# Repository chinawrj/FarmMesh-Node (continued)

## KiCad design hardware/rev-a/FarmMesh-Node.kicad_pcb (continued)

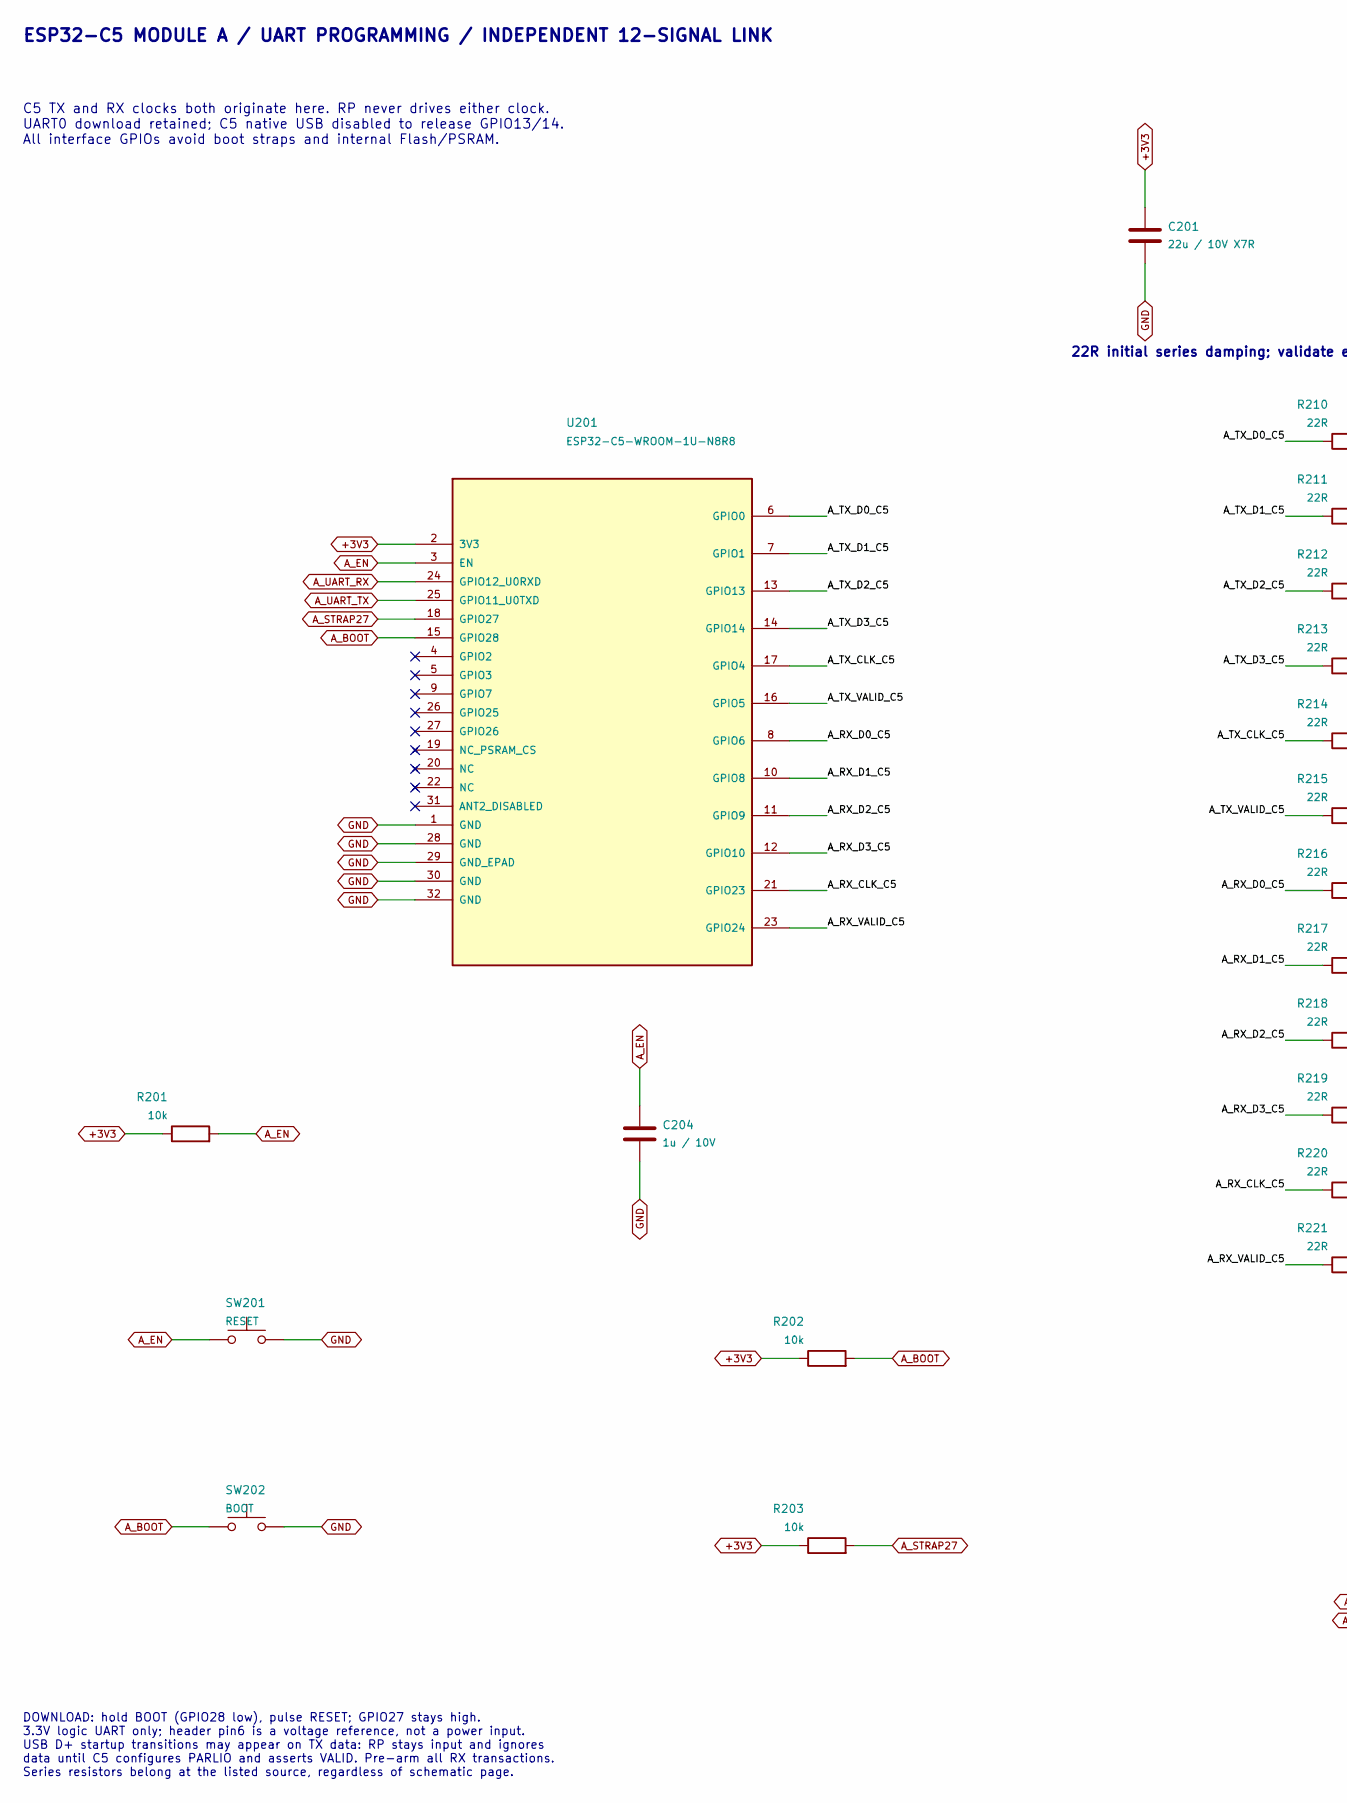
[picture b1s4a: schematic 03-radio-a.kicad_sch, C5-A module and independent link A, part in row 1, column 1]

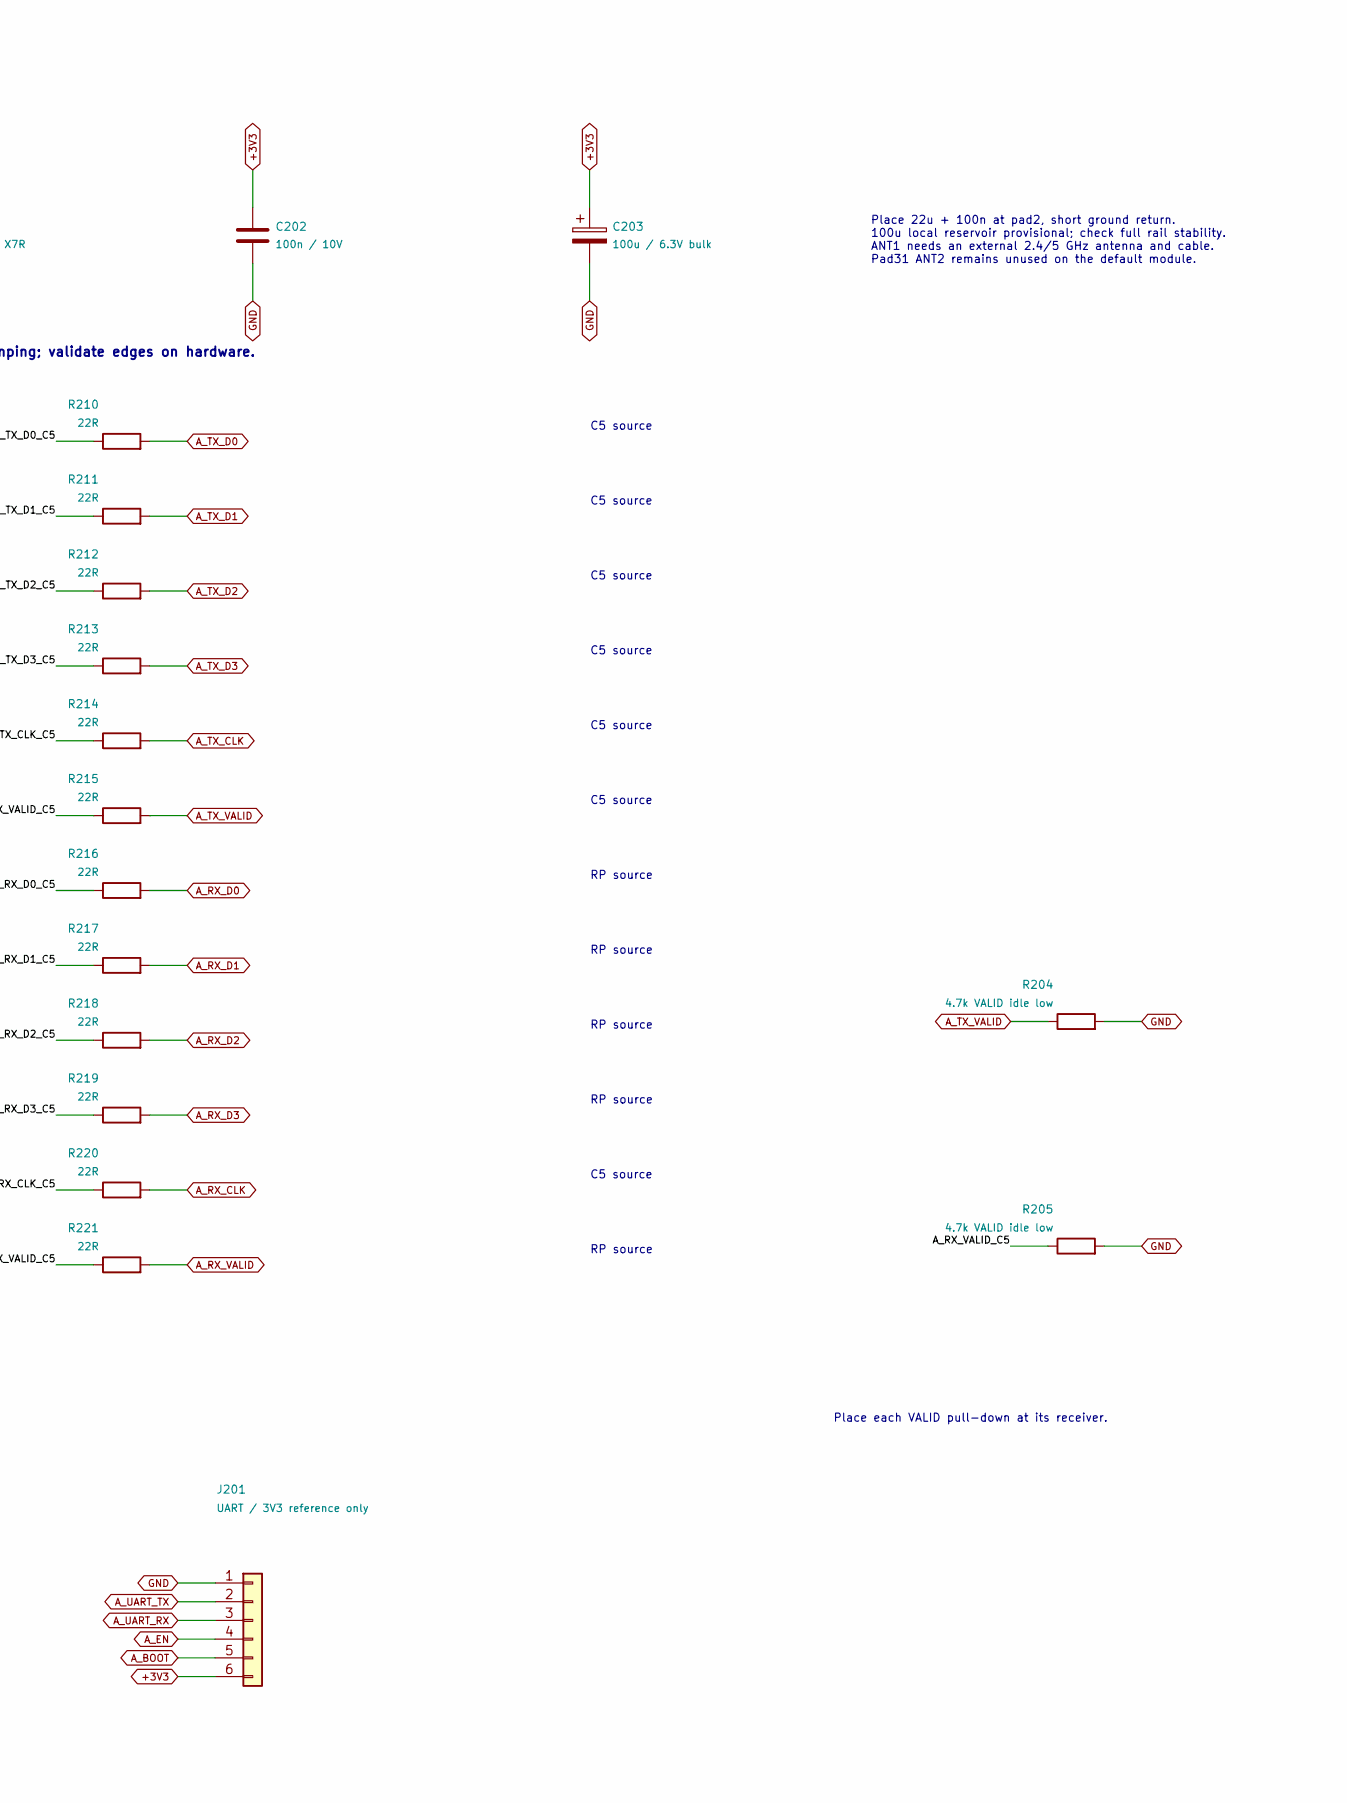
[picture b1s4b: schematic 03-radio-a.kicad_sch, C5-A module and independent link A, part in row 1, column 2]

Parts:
C201: 22u / 10V X7R; C_0805_2012Metric
C202: 100n / 10V; C_0603_1608Metric
C203: 100u / 6.3V bulk; CP_Elec_6.3x5.8
C204: 1u / 10V; C_0603_1608Metric
J201: UART / 3V3 reference only; PinHeader_1x06_P2.54mm_Vertical
R201, R202, R203: 10k; R_0603_1608Metric
R204, R205: 4.7k VALID idle low; R_0603_1608Metric
R210, R211, R212, R213, R214, R215, R216, R217, R218, R219, R220, R221: 22R; R_0603_1608Metric
SW201: RESET; SW_Push_1P1T_NO_E-Switch_TL3301NxxxxxG
SW202: BOOT; SW_Push_1P1T_NO_E-Switch_TL3301NxxxxxG
U201: ESP32-C5-WROOM-1U-N8R8; ESP32-C5-WROOM-1U; MPN ESP32-C5-WROOM-1U-N8R8

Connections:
+3V3: C201.1, C202.1, C203.1, J201.6, R201.1, R202.1, R203.1, U201.2 (3V3); also elsewhere on the board
/C5-A module and independent link A/A_RX_CLK_C5: R220.1, U201.21 (GPIO23)
/C5-A module and independent link A/A_RX_D0_C5: R216.1, U201.8 (GPIO6)
/C5-A module and independent link A/A_RX_D1_C5: R217.1, U201.10 (GPIO8)
/C5-A module and independent link A/A_RX_D2_C5: R218.1, U201.11 (GPIO9)
/C5-A module and independent link A/A_RX_D3_C5: R219.1, U201.12 (GPIO10)
/C5-A module and independent link A/A_RX_VALID_C5: R205.1, R221.1, U201.23 (GPIO24)
/C5-A module and independent link A/A_TX_CLK_C5: R214.1, U201.17 (GPIO4)
/C5-A module and independent link A/A_TX_D0_C5: R210.1, U201.6 (GPIO0)
/C5-A module and independent link A/A_TX_D1_C5: R211.1, U201.7 (GPIO1)
/C5-A module and independent link A/A_TX_D2_C5: R212.1, U201.13 (GPIO13)
/C5-A module and independent link A/A_TX_D3_C5: R213.1, U201.14 (GPIO14)
/C5-A module and independent link A/A_TX_VALID_C5: R215.1, U201.16 (GPIO5)
A_BOOT: J201.5, R202.2, SW202.1, U201.15 (GPIO28)
A_EN: C204.1, J201.4, R201.2, SW201.1, U201.3 (EN)
A_RX_CLK: R220.2; also elsewhere on the board
A_RX_D0: R216.2; also elsewhere on the board
A_RX_D1: R217.2; also elsewhere on the board
A_RX_D2: R218.2; also elsewhere on the board
A_RX_D3: R219.2; also elsewhere on the board
A_RX_VALID: R221.2; also elsewhere on the board
A_STRAP27: R203.2, U201.18 (GPIO27)
A_TX_CLK: R214.2; also elsewhere on the board
A_TX_D0: R210.2; also elsewhere on the board
A_TX_D1: R211.2; also elsewhere on the board
A_TX_D2: R212.2; also elsewhere on the board
A_TX_D3: R213.2; also elsewhere on the board
A_TX_VALID: R204.1, R215.2; also elsewhere on the board
A_UART_RX: J201.3, U201.24 (GPIO12_U0RXD)
A_UART_TX: J201.2, U201.25 (GPIO11_U0TXD)
GND: C201.2, C202.2, C203.2, C204.2, J201.1, R204.2, R205.2, SW201.2, SW202.2, U201.1 (GND), U201.28 (GND), U201.29 (GND_EPAD), U201.30 (GND), U201.32 (GND); also elsewhere on the board

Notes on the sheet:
22R initial series damping; validate edges on hardware.
ESP32-C5 MODULE A / UART PROGRAMMING / INDEPENDENT 12-SIGNAL LINK
Place each VALID pull-down at its receiver.
C5 source
RP source
Place 22u + 100n at pad2, short ground return. 100u local reservoir provisional; check full rail stability. ANT1 needs an external 2.4/5 GHz antenna and cable. Pad31 ANT2 remains unused on the default module.
C5 TX and RX clocks both originate here. RP never drives either clock. UART0 download retained; C5 native USB disabled to release GPIO13/14. All interface GPIOs avoid boot straps and internal Flash/PSRAM.
DOWNLOAD: hold BOOT (GPIO28 low), pulse RESET; GPIO27 stays high. 3.3V logic UART only; header pin6 is a voltage reference, not a power input. USB D+ startup transitions may appear on TX data: RP stays input and ignores data until C5 configures PARLIO and asserts VALID. Pre-arm all RX transactions.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

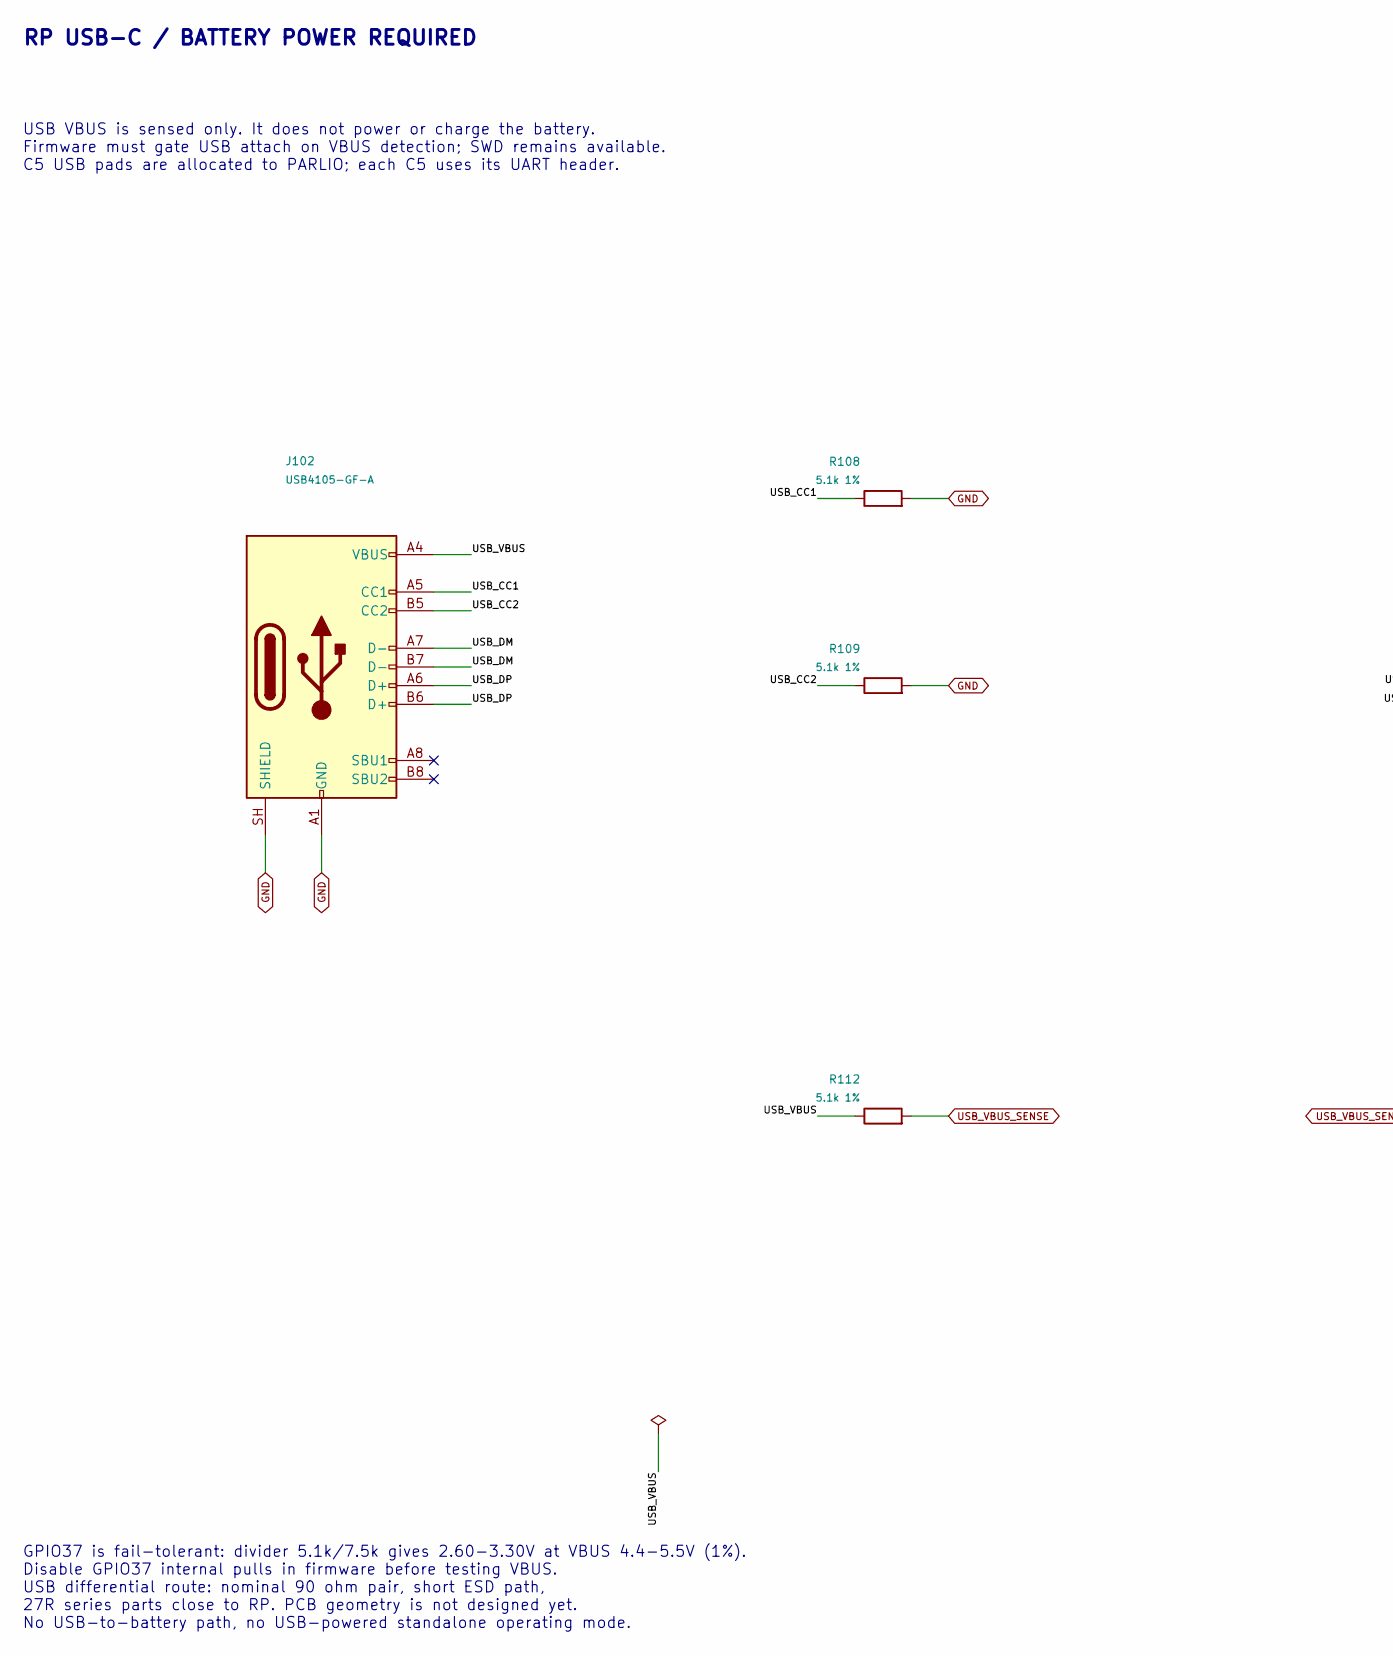
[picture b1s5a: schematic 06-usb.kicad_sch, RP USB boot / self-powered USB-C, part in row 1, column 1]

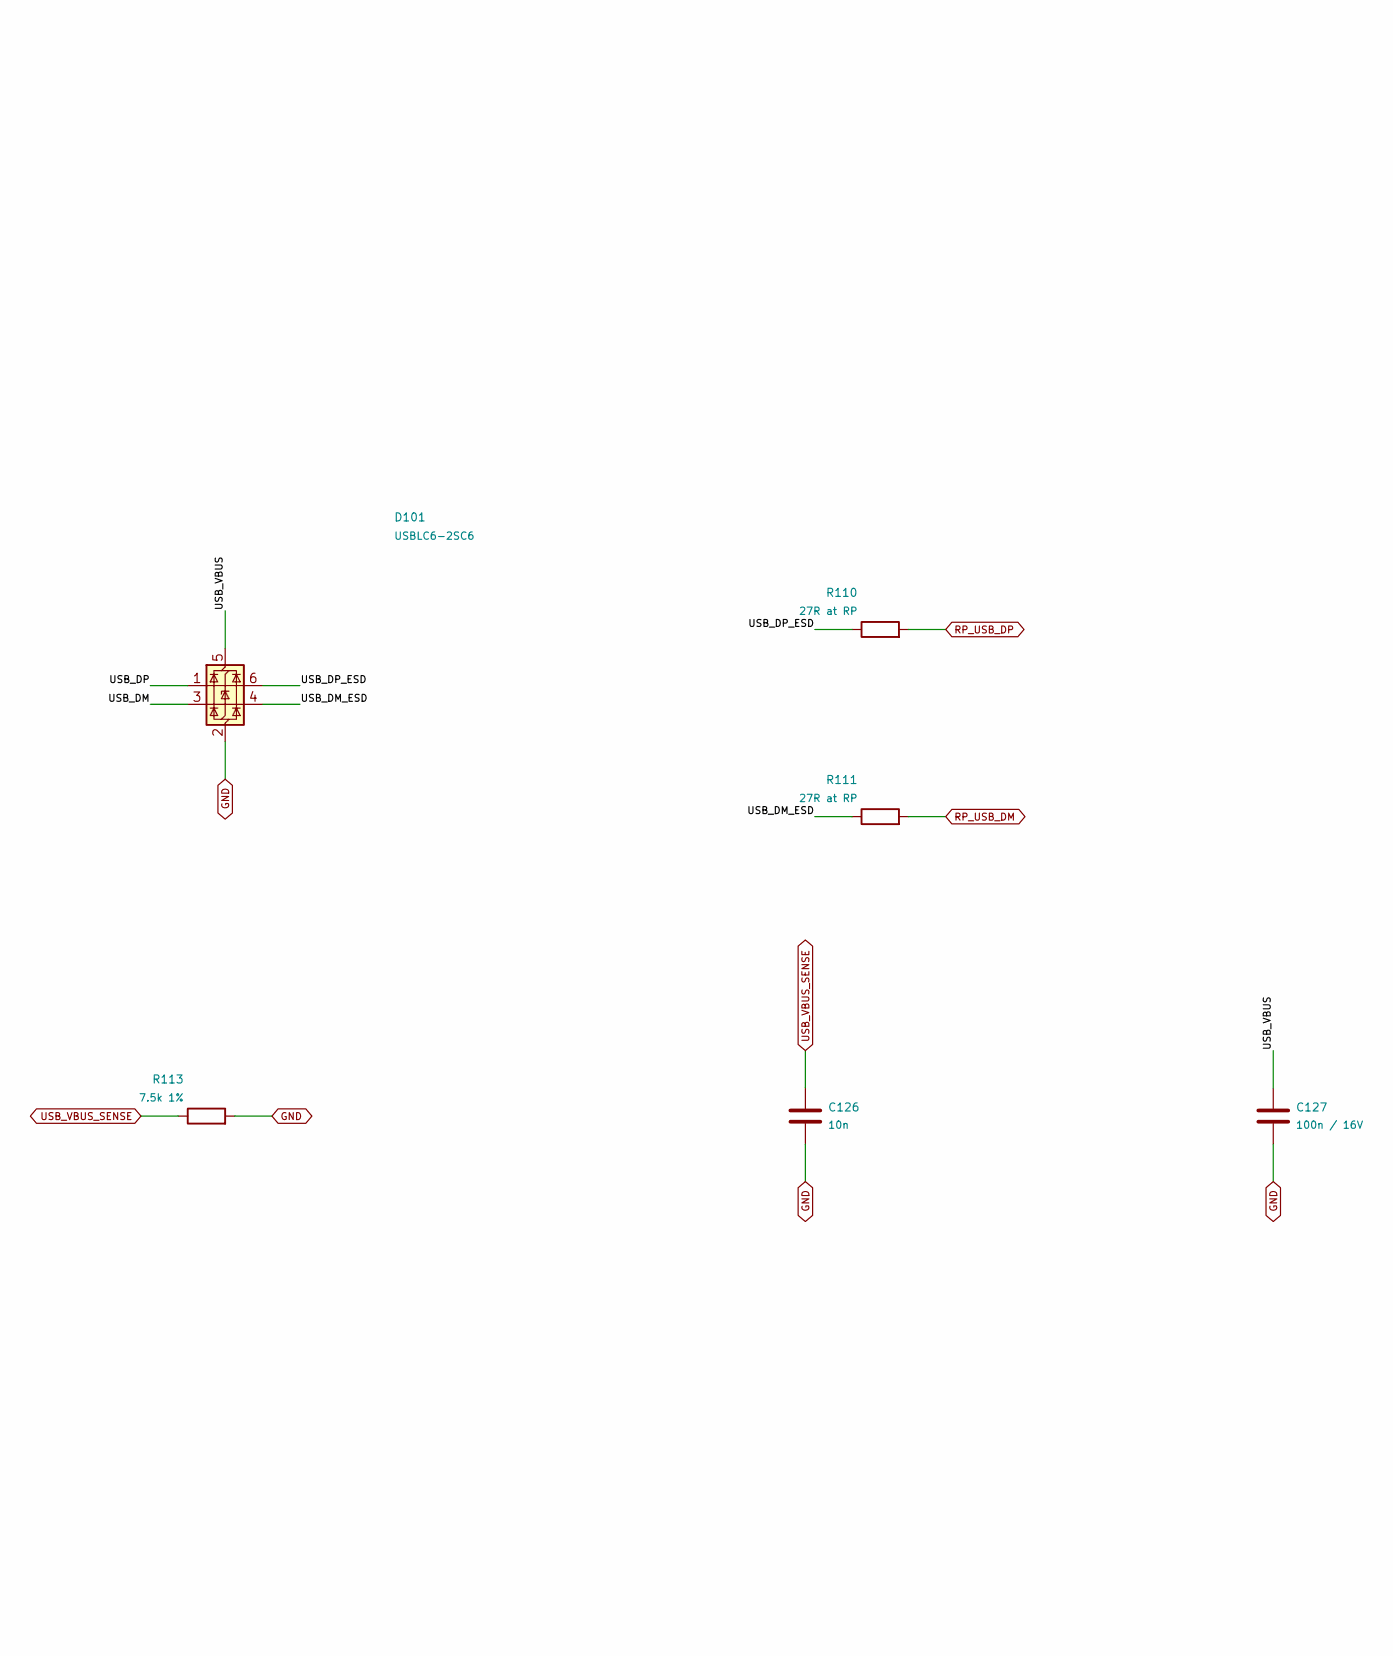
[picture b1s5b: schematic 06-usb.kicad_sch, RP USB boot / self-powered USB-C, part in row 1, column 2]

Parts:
C126: 10n; C_0603_1608Metric
C127: 100n / 16V; C_0603_1608Metric
D101: USBLC6-2SC6; SOT-23-6; MPN USBLC6-2SC6
J102: USB4105-GF-A; USB_C_Receptacle_GCT_USB4105-xx-A_16P_TopMnt_Horizontal; MPN USB4105-GF-A
R108, R109, R112: 5.1k 1%; R_0603_1608Metric
R110, R111: 27R at RP; R_0603_1608Metric
R113: 7.5k 1%; R_0603_1608Metric

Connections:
/RP USB boot / self-powered USB-C/USB_CC1: J102.A5 (CC1), R108.1
/RP USB boot / self-powered USB-C/USB_CC2: J102.B5 (CC2), R109.1
/RP USB boot / self-powered USB-C/USB_DM: D101.3 (I/O2), J102.A7 (D-), J102.B7 (D-)
/RP USB boot / self-powered USB-C/USB_DP: D101.1 (I/O1), J102.A6 (D+), J102.B6 (D+)
/RP USB boot / self-powered USB-C/USB_VBUS: C127.1, D101.5 (VBUS), J102.A4 (VBUS), J102.A9 (VBUS), J102.B4 (VBUS), J102.B9 (VBUS), R112.1; also elsewhere on the board
GND: C126.2, C127.2, D101.2 (GND), J102.A1 (GND), J102.A12 (GND), J102.B1 (GND), J102.B12 (GND), J102.SH (SHIELD), R108.2, R109.2, R113.2; also elsewhere on the board
RP_USB_DM: R111.2; also elsewhere on the board
RP_USB_DP: R110.2; also elsewhere on the board
USB_VBUS_SENSE: C126.1, R112.2, R113.1; also elsewhere on the board

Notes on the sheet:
GPIO37 is fail-tolerant: divider 5.1k/7.5k gives 2.60-3.30V at VBUS 4.4-5.5V (1%). Disable GPIO37 internal pulls in firmware before testing VBUS. USB differential route: nominal 90 ohm pair, short ESD path, 27R series parts close to RP. PCB geometry is not designed yet. No USB-to-battery path, no U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
USB VBUS is sensed only. It does not power or charge the battery. Firmware must gate USB attach on VBUS detection; SWD remains available. C5 USB pads are allocated to PARLIO; each C5 uses its UART header.
RP USB-C / BATTERY POWER REQUIRED

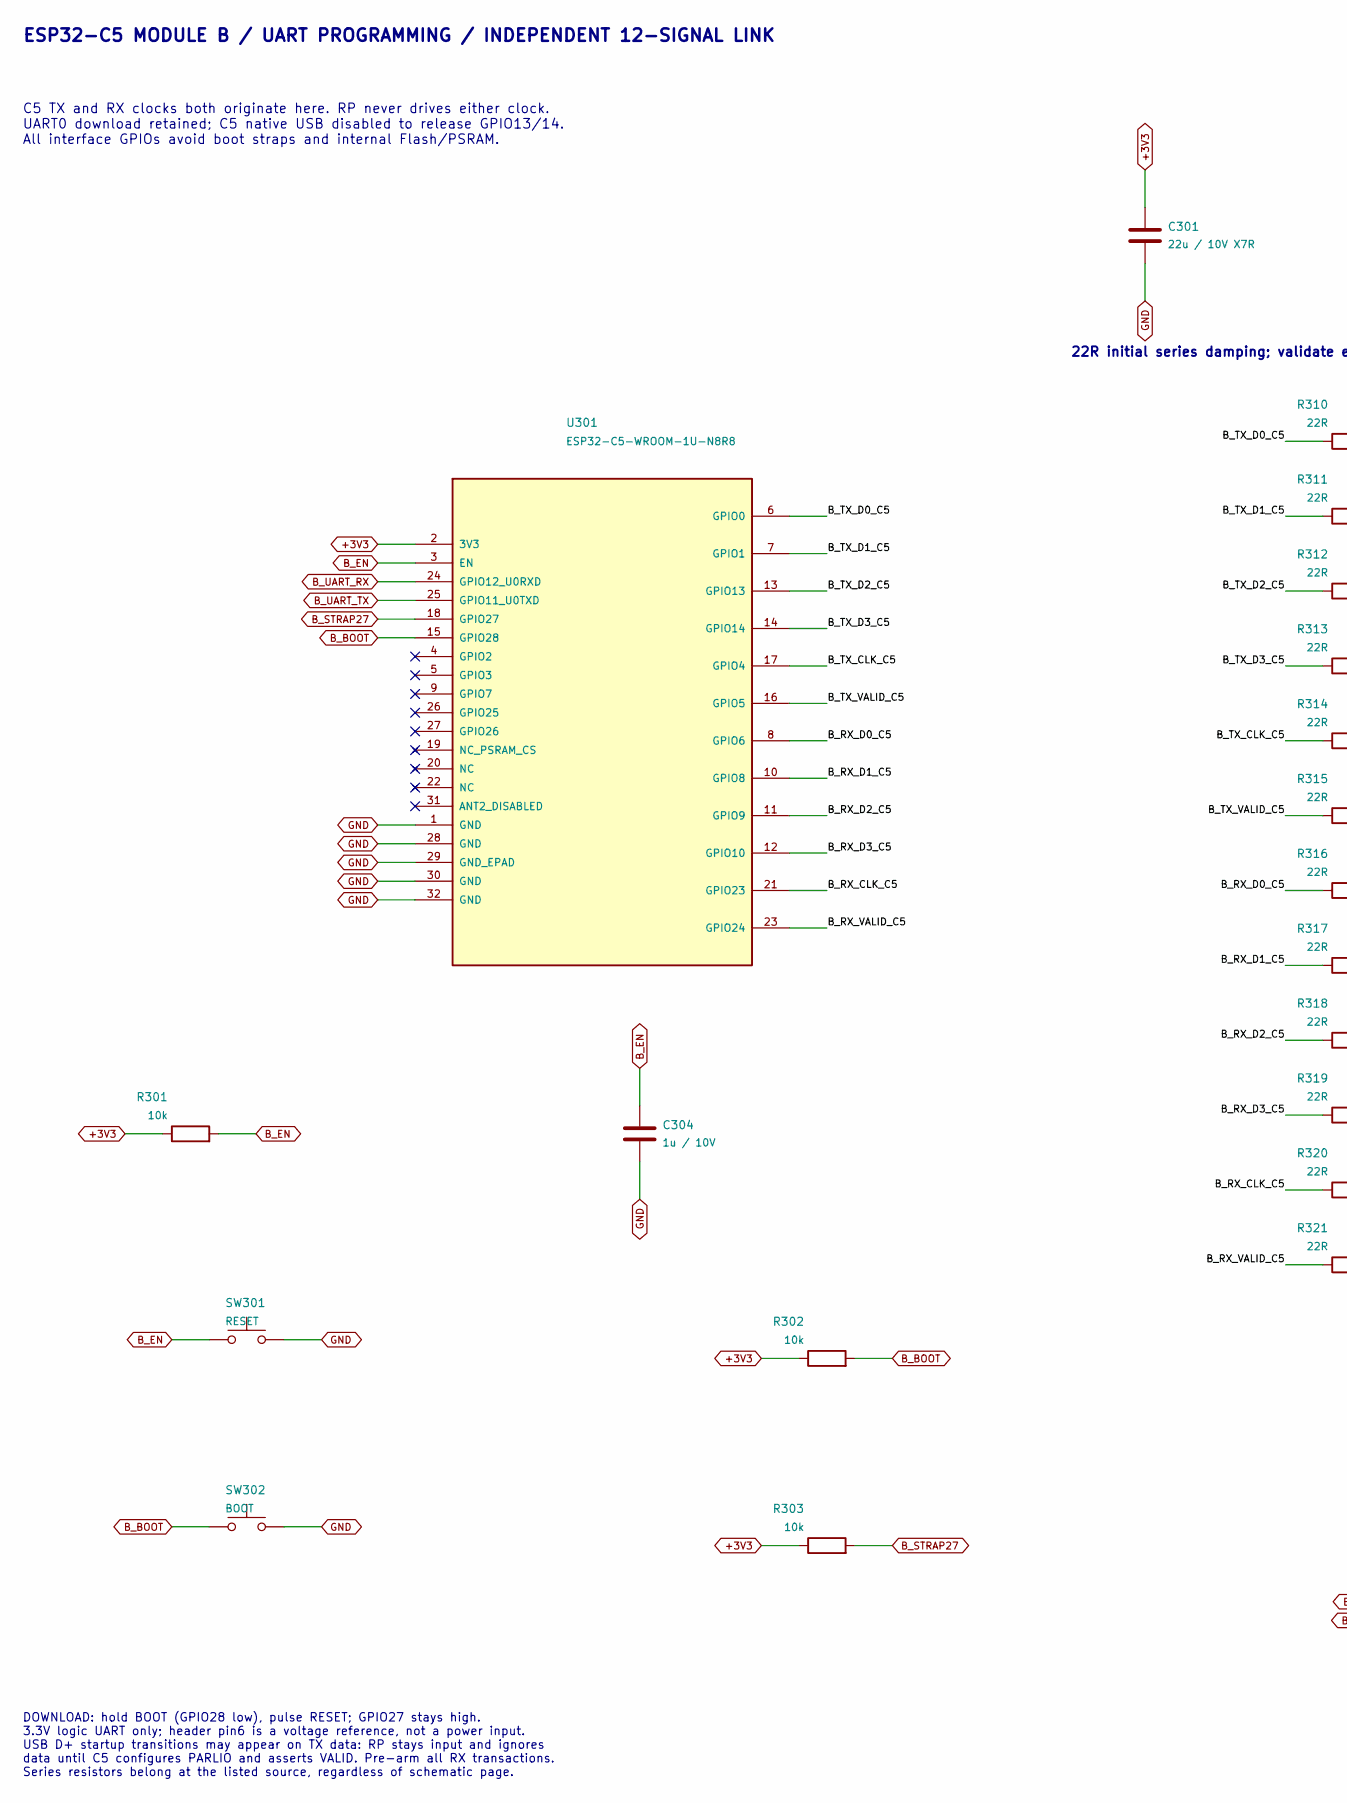
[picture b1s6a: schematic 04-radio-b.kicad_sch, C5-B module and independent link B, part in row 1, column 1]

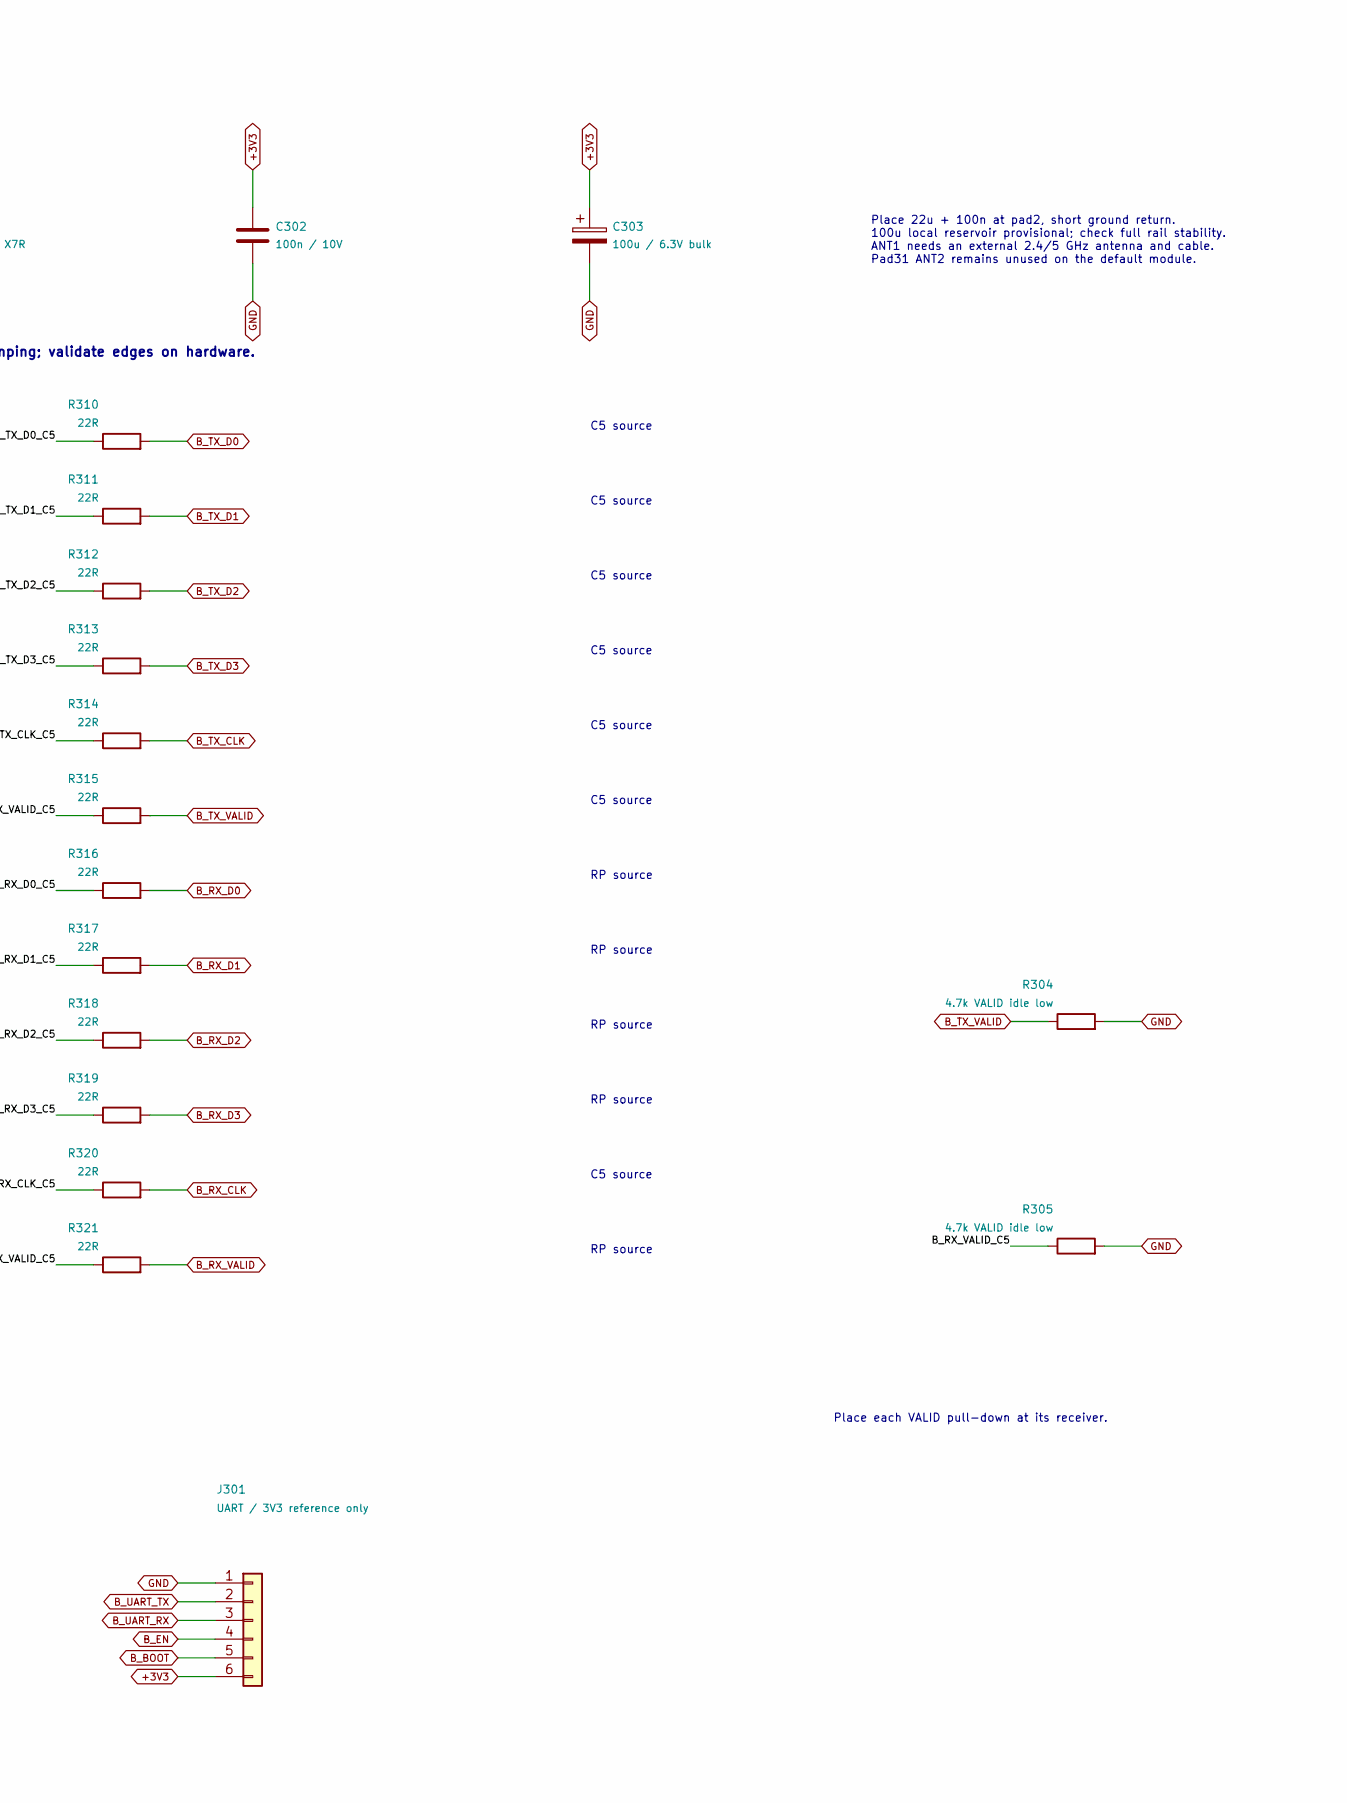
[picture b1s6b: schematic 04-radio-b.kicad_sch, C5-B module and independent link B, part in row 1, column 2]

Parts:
C301: 22u / 10V X7R; C_0805_2012Metric
C302: 100n / 10V; C_0603_1608Metric
C303: 100u / 6.3V bulk; CP_Elec_6.3x5.8
C304: 1u / 10V; C_0603_1608Metric
J301: UART / 3V3 reference only; PinHeader_1x06_P2.54mm_Vertical
R301, R302, R303: 10k; R_0603_1608Metric
R304, R305: 4.7k VALID idle low; R_0603_1608Metric
R310, R311, R312, R313, R314, R315, R316, R317, R318, R319, R320, R321: 22R; R_0603_1608Metric
SW301: RESET; SW_Push_1P1T_NO_E-Switch_TL3301NxxxxxG
SW302: BOOT; SW_Push_1P1T_NO_E-Switch_TL3301NxxxxxG
U301: ESP32-C5-WROOM-1U-N8R8; ESP32-C5-WROOM-1U; MPN ESP32-C5-WROOM-1U-N8R8

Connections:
+3V3: C301.1, C302.1, C303.1, J301.6, R301.1, R302.1, R303.1, U301.2 (3V3); also elsewhere on the board
/C5-B module and independent link B/B_RX_CLK_C5: R320.1, U301.21 (GPIO23)
/C5-B module and independent link B/B_RX_D0_C5: R316.1, U301.8 (GPIO6)
/C5-B module and independent link B/B_RX_D1_C5: R317.1, U301.10 (GPIO8)
/C5-B module and independent link B/B_RX_D2_C5: R318.1, U301.11 (GPIO9)
/C5-B module and independent link B/B_RX_D3_C5: R319.1, U301.12 (GPIO10)
/C5-B module and independent link B/B_RX_VALID_C5: R305.1, R321.1, U301.23 (GPIO24)
/C5-B module and independent link B/B_TX_CLK_C5: R314.1, U301.17 (GPIO4)
/C5-B module and independent link B/B_TX_D0_C5: R310.1, U301.6 (GPIO0)
/C5-B module and independent link B/B_TX_D1_C5: R311.1, U301.7 (GPIO1)
/C5-B module and independent link B/B_TX_D2_C5: R312.1, U301.13 (GPIO13)
/C5-B module and independent link B/B_TX_D3_C5: R313.1, U301.14 (GPIO14)
/C5-B module and independent link B/B_TX_VALID_C5: R315.1, U301.16 (GPIO5)
B_BOOT: J301.5, R302.2, SW302.1, U301.15 (GPIO28)
B_EN: C304.1, J301.4, R301.2, SW301.1, U301.3 (EN)
B_RX_CLK: R320.2; also elsewhere on the board
B_RX_D0: R316.2; also elsewhere on the board
B_RX_D1: R317.2; also elsewhere on the board
B_RX_D2: R318.2; also elsewhere on the board
B_RX_D3: R319.2; also elsewhere on the board
B_RX_VALID: R321.2; also elsewhere on the board
B_STRAP27: R303.2, U301.18 (GPIO27)
B_TX_CLK: R314.2; also elsewhere on the board
B_TX_D0: R310.2; also elsewhere on the board
B_TX_D1: R311.2; also elsewhere on the board
B_TX_D2: R312.2; also elsewhere on the board
B_TX_D3: R313.2; also elsewhere on the board
B_TX_VALID: R304.1, R315.2; also elsewhere on the board
B_UART_RX: J301.3, U301.24 (GPIO12_U0RXD)
B_UART_TX: J301.2, U301.25 (GPIO11_U0TXD)
GND: C301.2, C302.2, C303.2, C304.2, J301.1, R304.2, R305.2, SW301.2, SW302.2, U301.1 (GND), U301.28 (GND), U301.29 (GND_EPAD), U301.30 (GND), U301.32 (GND); also elsewhere on the board

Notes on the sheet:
Place each VALID pull-down at its receiver.
C5 source
RP source
ESP32-C5 MODULE B / UART PROGRAMMING / INDEPENDENT 12-SIGNAL LINK
DOWNLOAD: hold BOOT (GPIO28 low), pulse RESET; GPIO27 stays high. 3.3V logic UART only; header pin6 is a voltage reference, not a power input. USB D+ startup transitions may appear on TX data: RP stays input and ignores data until C5 configures PARLIO and asserts VALID. Pre-arm all RX transactions.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
22R initial series damping; validate edges on hardware.
C5 TX and RX clocks both originate here. RP never drives either clock. UART0 download retained; C5 native USB disabled to release GPIO13/14. All interface GPIOs avoid boot straps and internal Flash/PSRAM.
Place 22u + 100n at pad2, short ground return. 100u local reservoir provisional; check full rail stability. ANT1 needs an external 2.4/5 GHz antenna and cable. Pad31 ANT2 remains unused on the default module.
